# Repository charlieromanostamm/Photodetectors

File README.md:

# Photodetectors
This is the repo for the photodetector projects

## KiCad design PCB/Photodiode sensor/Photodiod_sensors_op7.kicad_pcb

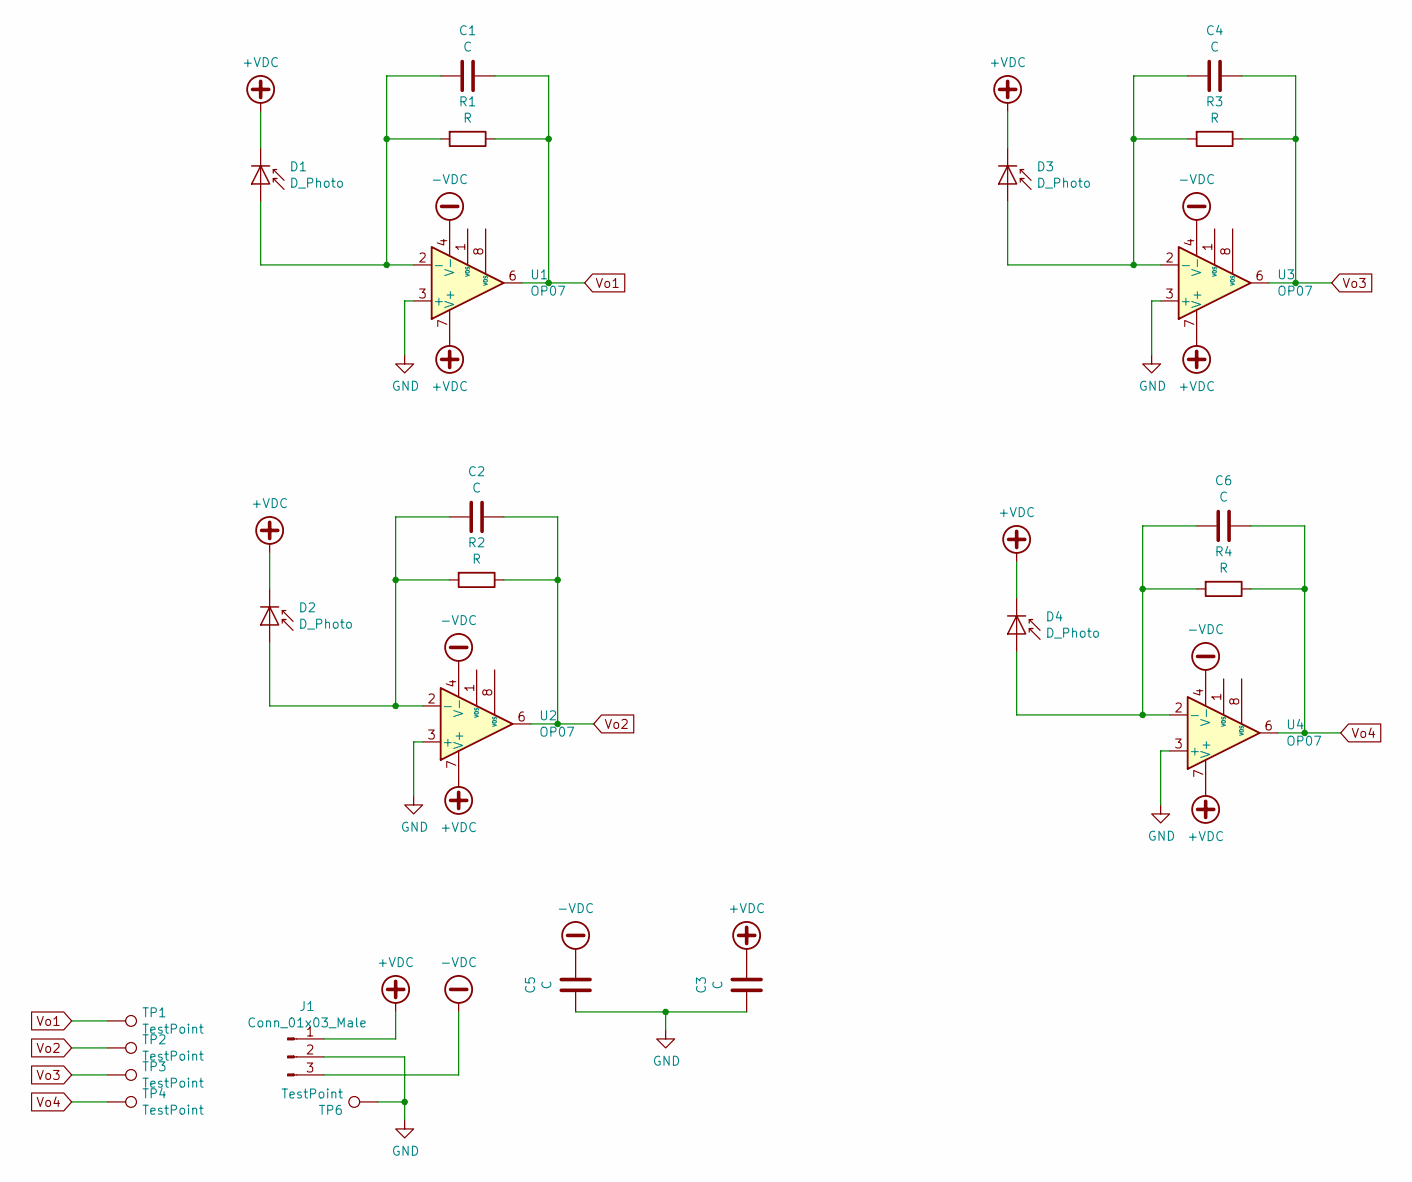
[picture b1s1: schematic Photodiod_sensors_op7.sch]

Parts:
C1, C2, C3, C4, C5, C6: C; C_1206_3216Metric
D1, D2, D3, D4: D_Photo; BPW34
J1: Conn_01x03_Male; TerminalBlock_bornier-3_P5.08mm
R1, R2, R3, R4: R; R_1206_3216Metric
TP1, TP2, TP3, TP4, TP6: TestPoint; Pin_D1.0mm_L10.0mm
U1, U2, U3, U4: OP07; DIP-8_W7.62mm_LongPads

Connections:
+VDC: C3.1, D1.1 (K), D2.1 (K), D3.1 (K), D4.1 (K), J1.1, U1.7 (V+), U2.7 (V+), U3.7 (V+), U4.7 (V+)
-VDC: C5.1, J1.3, U1.4 (V-), U2.4 (V-), U3.4 (V-), U4.4 (V-)
GND: C3.2, C5.2, J1.2, TP6.1, U1.3 (+), U2.3 (+), U3.3 (+), U4.3 (+)
unnamed: C1.2, D1.2 (A), R1.2, U1.2 (-)
unnamed: C2.2, D2.2 (A), R2.2, U2.2 (-)
unnamed: C4.2, D3.2 (A), R3.2, U3.2 (-)
unnamed: C6.2, D4.2 (A), R4.2, U4.2 (-)
Vo1: C1.1, R1.1, TP1.1, U1.6
Vo2: C2.1, R2.1, TP2.1, U2.6
Vo3: C4.1, R3.1, TP3.1, U3.6
Vo4: C6.1, R4.1, TP4.1, U4.6

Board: 2 copper layers, 24 parts (0 on the bottom side), 11 nets, no tracks yet.

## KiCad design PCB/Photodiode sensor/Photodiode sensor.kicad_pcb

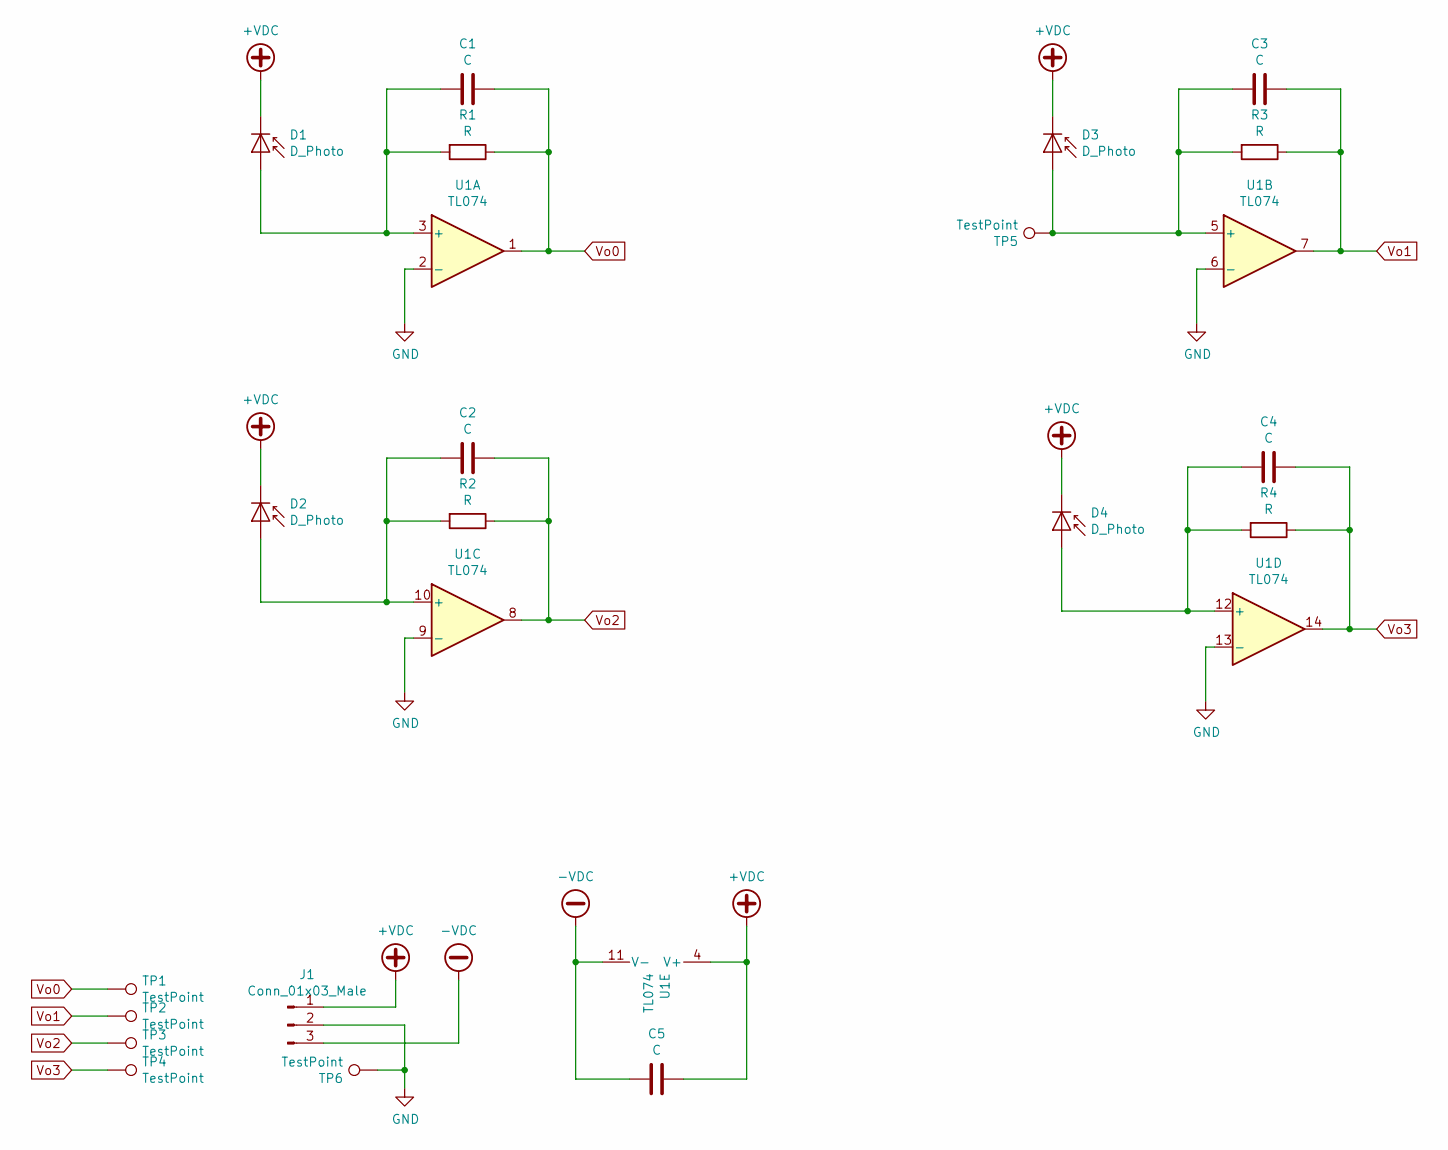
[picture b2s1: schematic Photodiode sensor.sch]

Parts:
C1, C2, C3, C4, C5: C; C_1206_3216Metric
D1, D2, D3, D4: D_Photo; BPW34
J1: Conn_01x03_Male; TerminalBlock_bornier-3_P5.08mm
R1, R2, R3, R4: R; R_Axial_DIN0207_L6.3mm_D2.5mm_P2.54mm_Vertical
TP1, TP2, TP3, TP4, TP5, TP6: TestPoint; Pin_D1.0mm_L10.0mm
U1: TL074; DIP-14_W7.62mm_LongPads

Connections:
+VDC: C5.1, D1.1 (K), D2.1 (K), D3.1 (K), D4.1 (K), J1.1, U1.4 (V+)
-VDC: C5.2, J1.3, U1.11 (V-)
GND: J1.2, TP6.1, U1.2 (-), U1.6 (-), U1.9 (-), U1.13 (-)
unnamed: C1.2, D1.2 (A), R1.2, U1.3 (+)
unnamed: C2.2, D2.2 (A), R2.2, U1.10 (+)
unnamed: C3.2, D3.2 (A), R3.2, TP5.1, U1.5 (+)
unnamed: C4.2, D4.2 (A), R4.2, U1.12 (+)
Vo0: C1.1, R1.1, TP1.1, U1.1
Vo1: C3.1, R3.1, TP2.1, U1.7
Vo2: C2.1, R2.1, TP3.1, U1.8
Vo3: C4.1, R4.1, TP4.1, U1.14

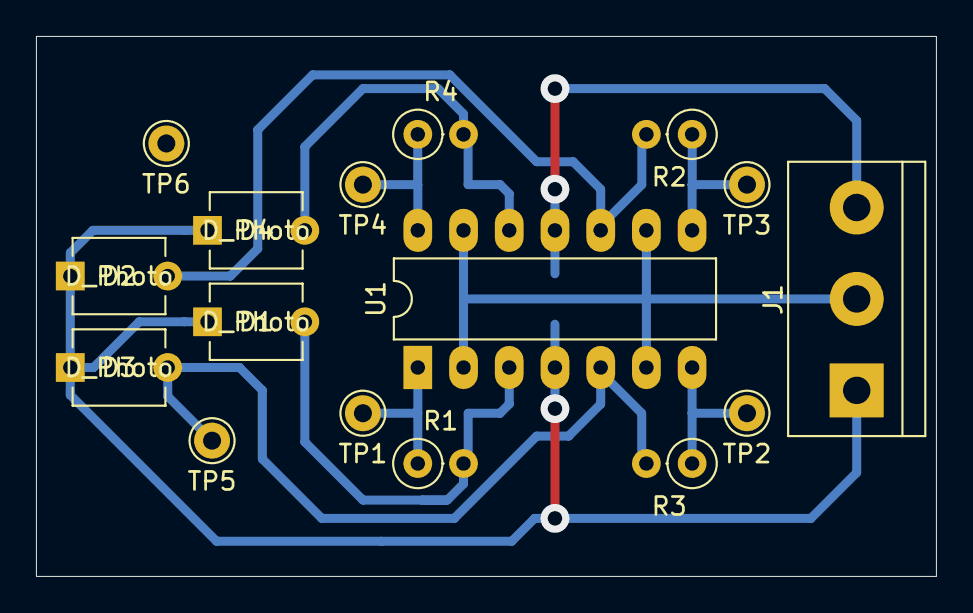
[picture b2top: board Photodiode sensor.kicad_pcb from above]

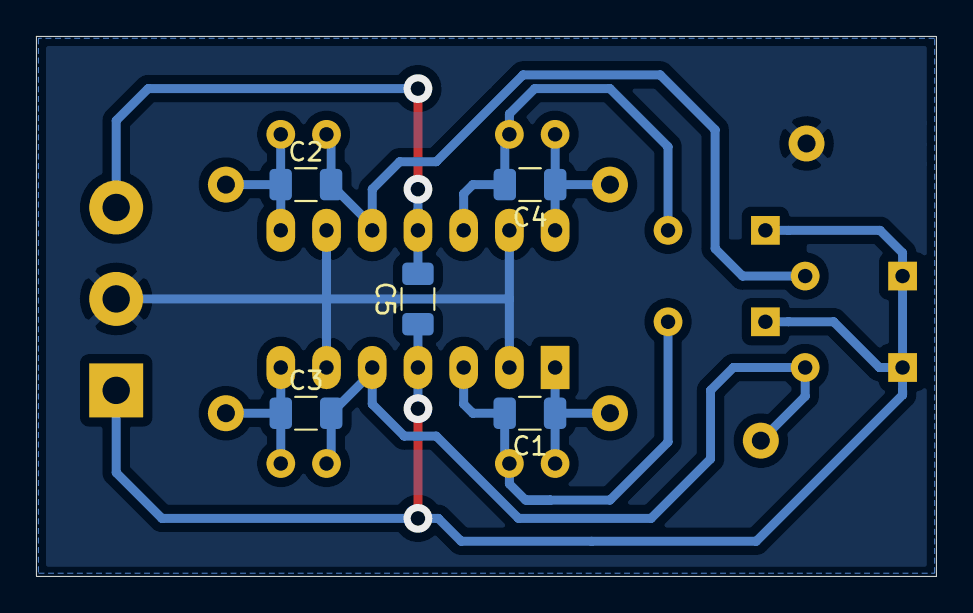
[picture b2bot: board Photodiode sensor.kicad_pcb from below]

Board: 2 copper layers, 50.0 x 30.0 mm, 21 parts (5 on the bottom side), 11 nets.

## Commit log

2021-07-29 include FIUBA designs
2021-08-11 pcb y spice
2021-09-01 new design for op7
2021-09-01 added ADC

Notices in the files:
parts and their libraries:
Copyright 2021 Accelerated Designs. All rights reserved.
